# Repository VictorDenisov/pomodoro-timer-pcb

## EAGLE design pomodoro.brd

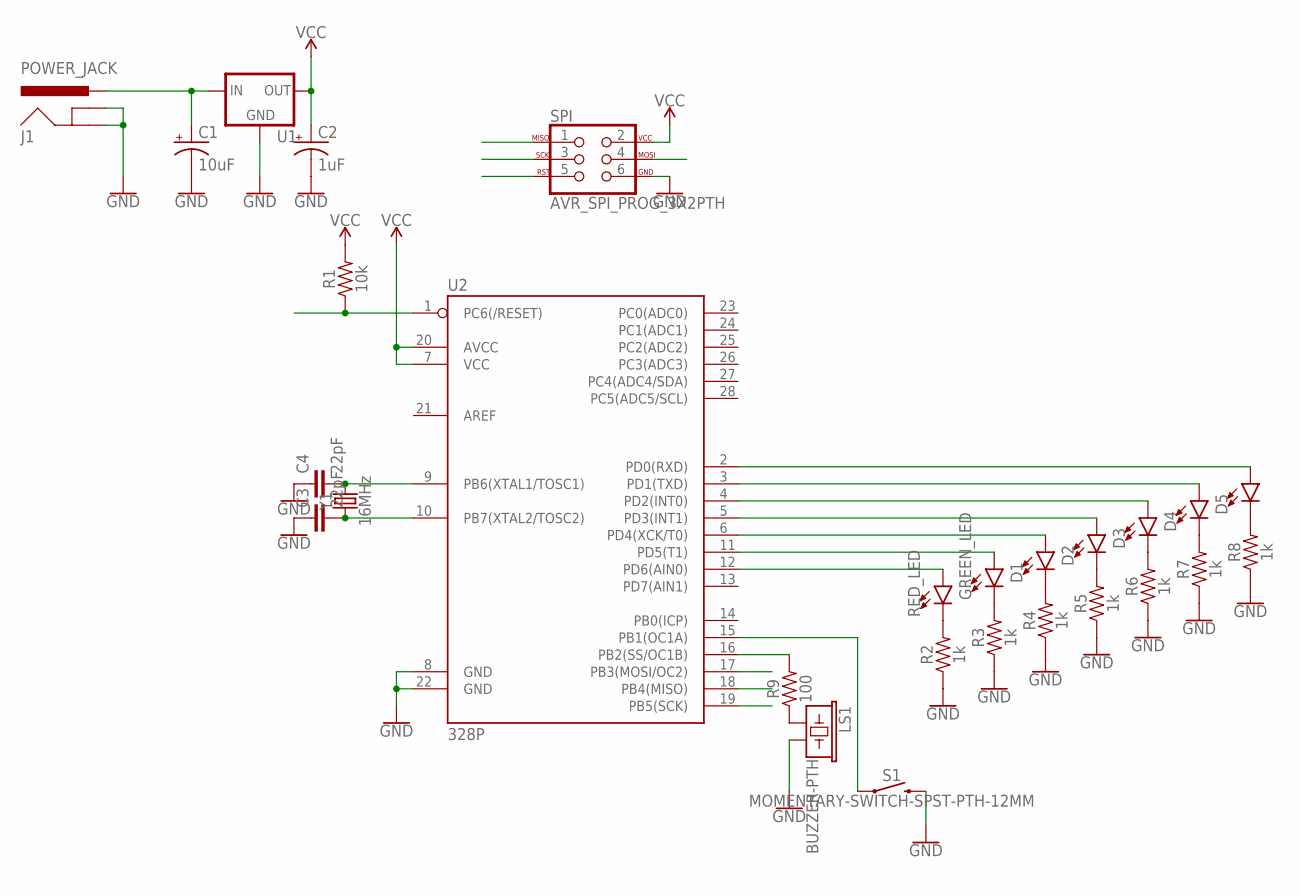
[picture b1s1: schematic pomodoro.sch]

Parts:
C1: 10uF; CPOL-RADIAL-2.5MM-5MM
C2: 1uF; CPOL-RADIAL-2.5MM-5MM
C3, C4: 22pF; CAP-PTH-2.54
D1, D2, D3, D4, D5: LED5MM; LED_5MM
GREEN_LED: LED5MM; LED_5MM
J1: POWER_JACK; POWER_JACK_PTH
LS1: BUZZER-PTH; BUZZER-12MM
R1: 10k; AXIAL-0.3
R2, R3, R4, R5, R6, R7, R8: 1k; AXIAL-0.3
R9: 100; AXIAL-0.3
RED_LED: LED5MM; LED_5MM
S1: MOMENTARY-SWITCH-SPST-PTH-12MM; TACTILE_SWITCH_PTH_12MM
SPI: AVR_SPI_PROG_3X2PTH; 2X3
U1: V_REG_78XX-TO-220; TO-220-ALT
U2: 328P; DIP28
Y1: 16MHz; HC49US

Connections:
GND: C1.2 (-), C2.2 (-), C3.1, C4.1, J1.GND, J1.GNDBREAK, LS1.- (2), R2.P$1 (1), R3.P$1 (1), R4.P$1 (1), R5.P$1 (1), R6.P$1 (1), R7.P$1 (1), R8.P$1 (1), S1.3 (2), SPI.6, U1.GND, U2.8 (GND), U2.22 (GND)
MISO: SPI.1, U2.18 (PB4(MISO))
MOSI: SPI.4, U2.17 (PB3(MOSI/OC2))
unnamed: R2.P$2 (2), RED_LED.K (C)
unnamed: C3.2, U2.10 (PB7(XTAL2/TOSC2)), Y1.1
unnamed: C4.2, U2.9 (PB6(XTAL1/TOSC1)), Y1.2
unnamed: GREEN_LED.K (C), R3.P$2 (2)
unnamed: D1.K (C), R4.P$2 (2)
unnamed: D2.K (C), R5.P$2 (2)
unnamed: D3.K (C), R6.P$2 (2)
unnamed: D4.K (C), R7.P$2 (2)
unnamed: D5.K (C), R8.P$2 (2)
unnamed: S1.1, U2.15 (PB1(OC1A))
unnamed: D5.A, U2.2 (PD0(RXD))
unnamed: D4.A, U2.3 (PD1(TXD))
unnamed: D3.A, U2.4 (PD2(INT0))
unnamed: D2.A, U2.5 (PD3(INT1))
unnamed: D1.A, U2.6 (PD4(XCK/T0))
unnamed: GREEN_LED.A, U2.11 (PD5(T1))
unnamed: RED_LED.A, U2.12 (PD6(AIN0))
unnamed: R9.P$2 (2), U2.16 (PB2(SS/OC1B))
unnamed: C1.1 (+), J1.PWR, U1.IN
unnamed: LS1.+ (1), R9.P$1 (1)
RST: R1.P$1 (1), SPI.5, U2.1 (PC6(/RESET))
SCK: SPI.3, U2.19 (PB5(SCK))
VCC: C2.1 (+), R1.P$2 (2), SPI.2, U1.OUT, U2.7 (VCC), U2.20 (AVCC)

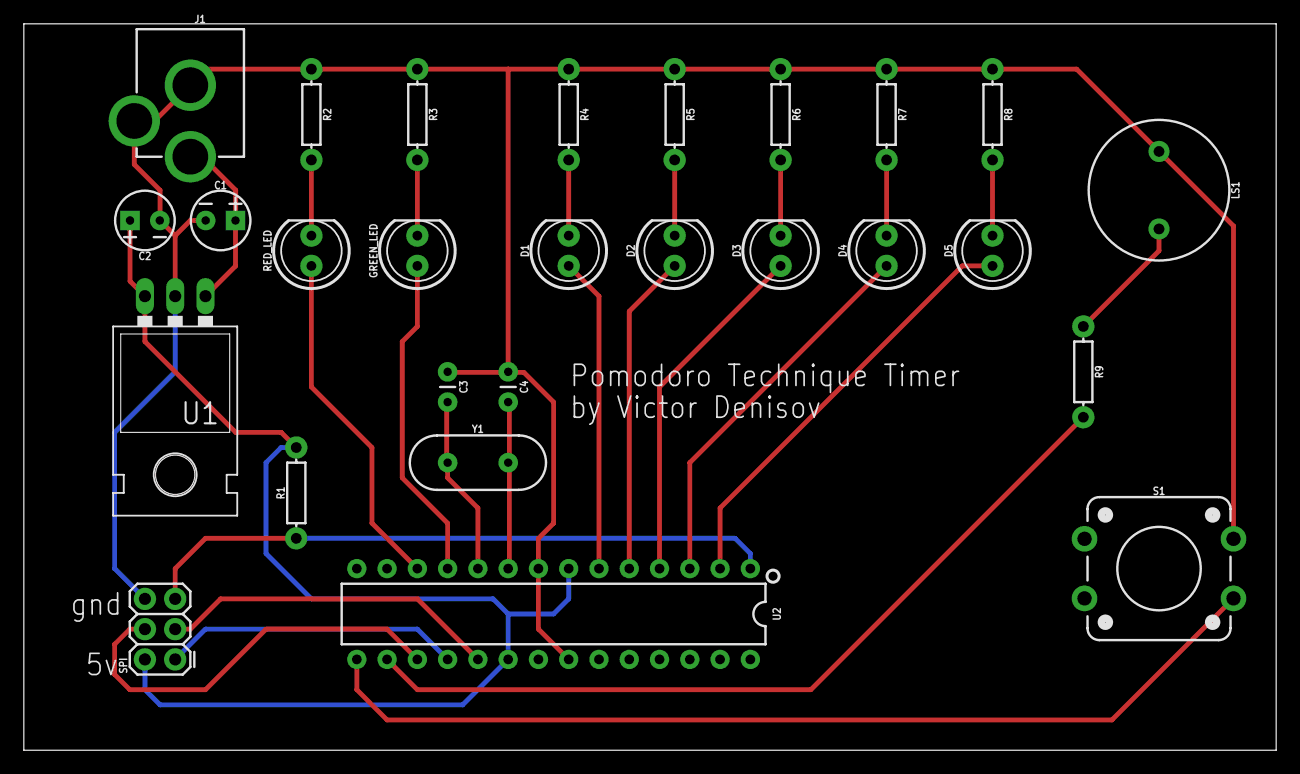
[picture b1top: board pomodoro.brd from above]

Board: 2 copper layers, 105.1 x 61.0 mm, 27 parts (0 on the bottom side), 26 nets.

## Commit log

2017-01-11 Initial import
2017-01-11 Move parts a bit
2017-01-11 Change layout
2017-01-12 Change values of elements

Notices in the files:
parts and their libraries:
SparkFun-Capacitors: Licensing: Creative Commons ShareAlike 4.0 International - https://creativecommons.org/licenses/by-sa/4.0
